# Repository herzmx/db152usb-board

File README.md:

# USB2DB15 Board

This board is intended to use NeoGeo Stick/Pad with DB15 port as USB controller on PC, MiSTer, Android, Raspberry Pi, Nintendo Switch, PS3 and PS4 (legacy), thanks to [GP2040](https://github.com/FeralAI/GP2040) gamepad firmware for the Raspberry Pi Pico.

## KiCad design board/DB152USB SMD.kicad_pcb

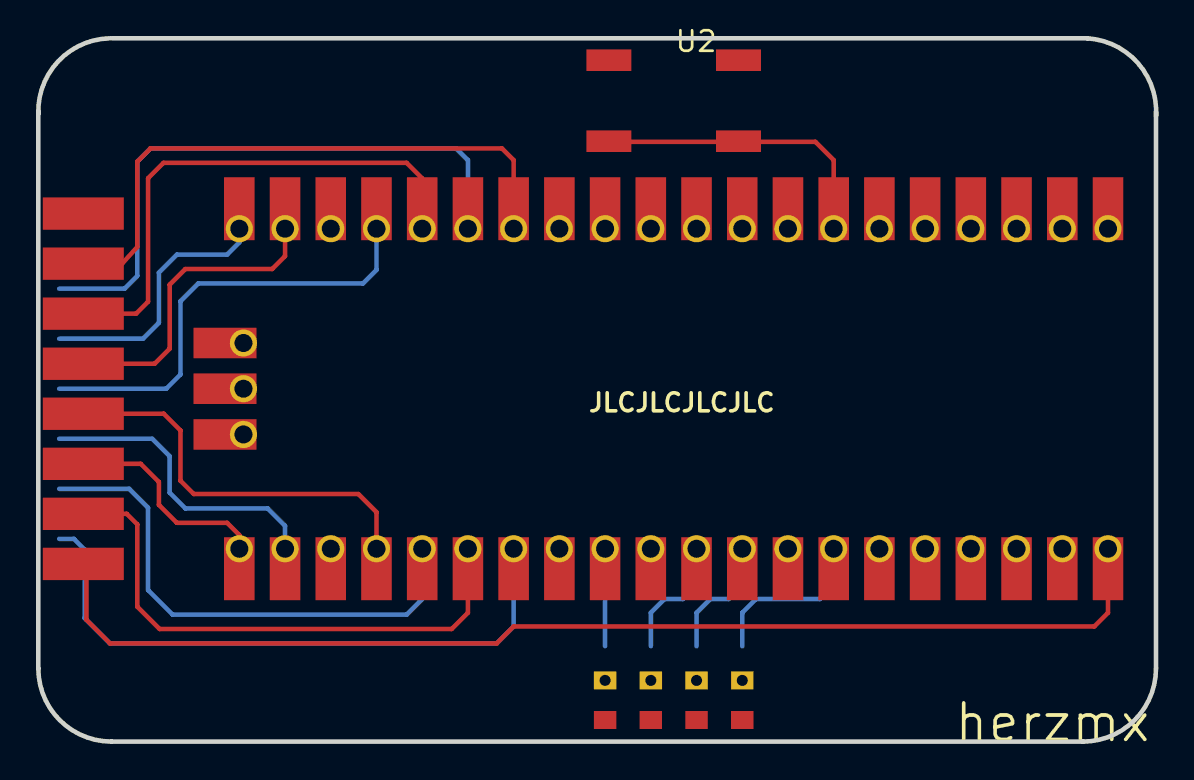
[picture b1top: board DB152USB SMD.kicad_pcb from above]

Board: 2 copper layers, 62.1 x 39.1 mm, 11 parts (0 on the bottom side), 28 nets.

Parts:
DB15-SMD: _; gge30799
LED1, LED2, LED3, LED4: LED0805-RD_GREEN-DOC
R1, R2, R3, R4: R0805-DOC
U2: SW-SMD_4P-L6.0-W6.0-P4.50-LS6.5
U4: PICO-PKG

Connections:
+5V: DB15-SMD.8, U4.40, U4.P$40
B1: DB15-SMD.13, U4.22, U4.P$22
B2: DB15-SMD.5, U4.24, U4.P$24
B3: DB15-SMD.12, U4.17, U4.P$17
B4: DB15-SMD.4, U4.19, U4.P$19
B5: DB15-SMD.10, U4.15, U4.P$15
B6: DB15-SMD.2, U4.14, U4.P$14
CAPTURE: U4.6, U4.P$6
D: DB15-SMD.7, U4.26, U4.P$26
GND: DB15-SMD.1, LED1.1, LED2.1, LED3.1, LED4.1, U2.1, U2.2, U4.3, U4.8, U4.13, U4.18, U4.23, U4.28, U4.33, U4.38, U4.P$3, U4.P$8, U4.P$13, U4.P$18, U4.P$23, U4.P$28, U4.P$33, U4.P$38
HOME: U2.3, U2.4, U4.7, U4.P$7
L: DB15-SMD.14, U4.25, U4.P$25
L1: U4.12, U4.P$12
L2: U4.11, U4.P$11
L3: U4.9, U4.P$9
LED1: R1.2, U4.29, U4.P$29
LED1R: LED1.2, R1.1
LED2: R2.2, U4.31, U4.P$31
LED2R: LED2.2, R2.1
LED3: R3.2, U4.32, U4.P$32
LED3R: LED3.2, R3.1
LED4: R4.2, U4.34, U4.P$34
LED4R: LED4.2, R4.1
R: DB15-SMD.6, U4.21, U4.P$21
R3: U4.10, U4.P$10
SELECT: DB15-SMD.3, U4.16, U4.P$16
START: DB15-SMD.11, U4.20, U4.P$20
U: DB15-SMD.15, U4.27, U4.P$27

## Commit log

2022-06-29 Fix typo
